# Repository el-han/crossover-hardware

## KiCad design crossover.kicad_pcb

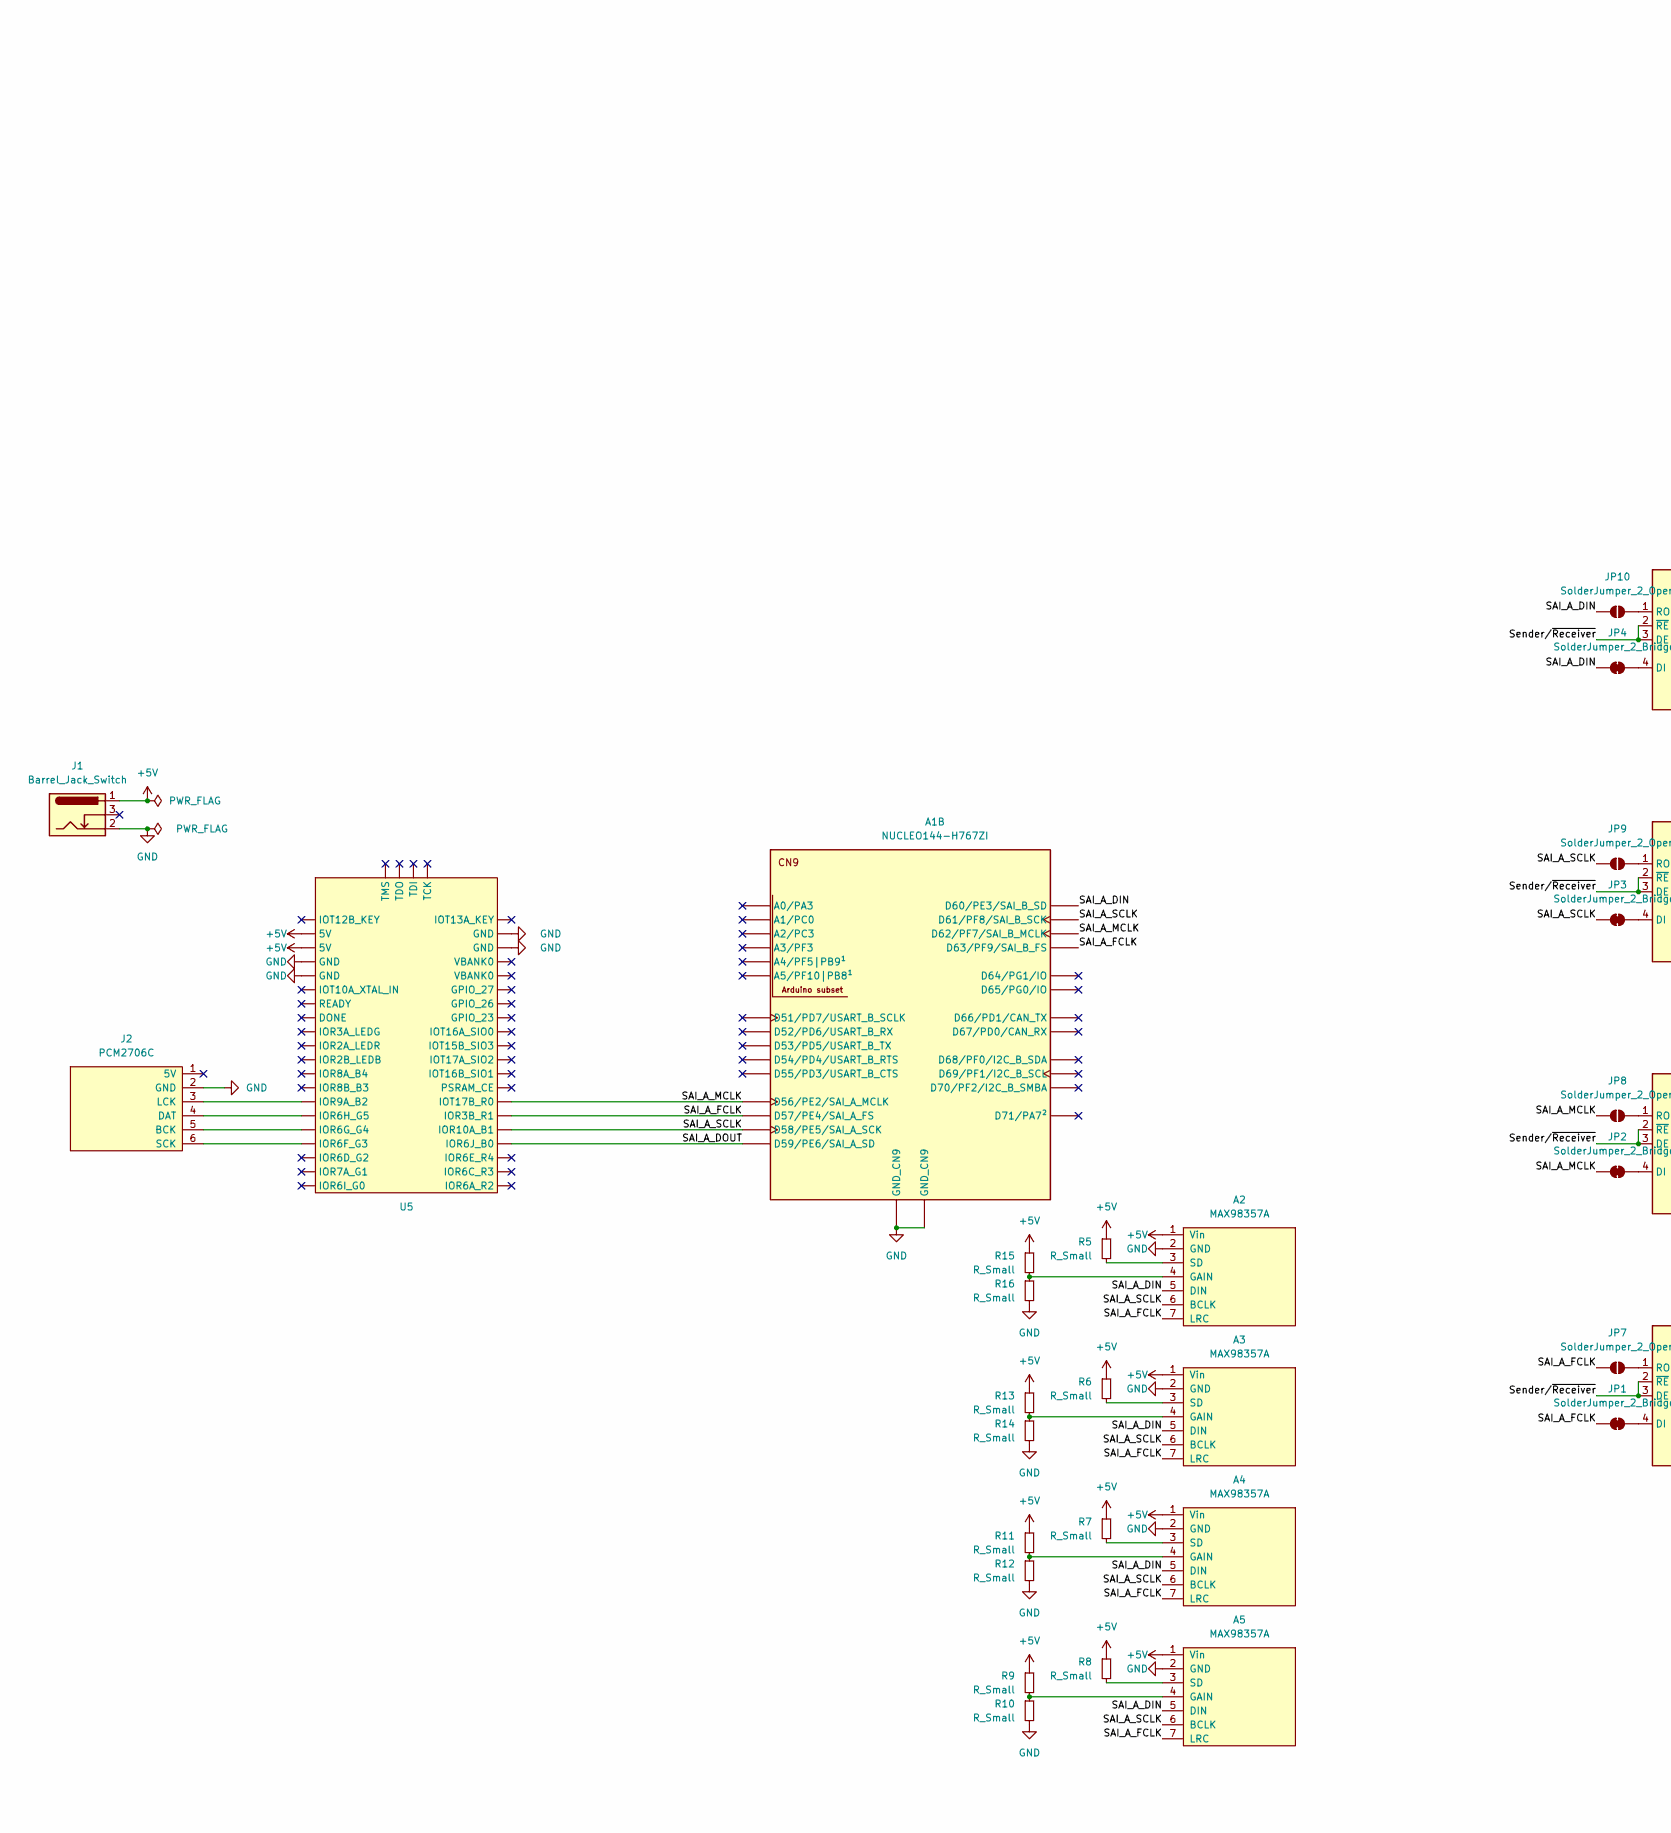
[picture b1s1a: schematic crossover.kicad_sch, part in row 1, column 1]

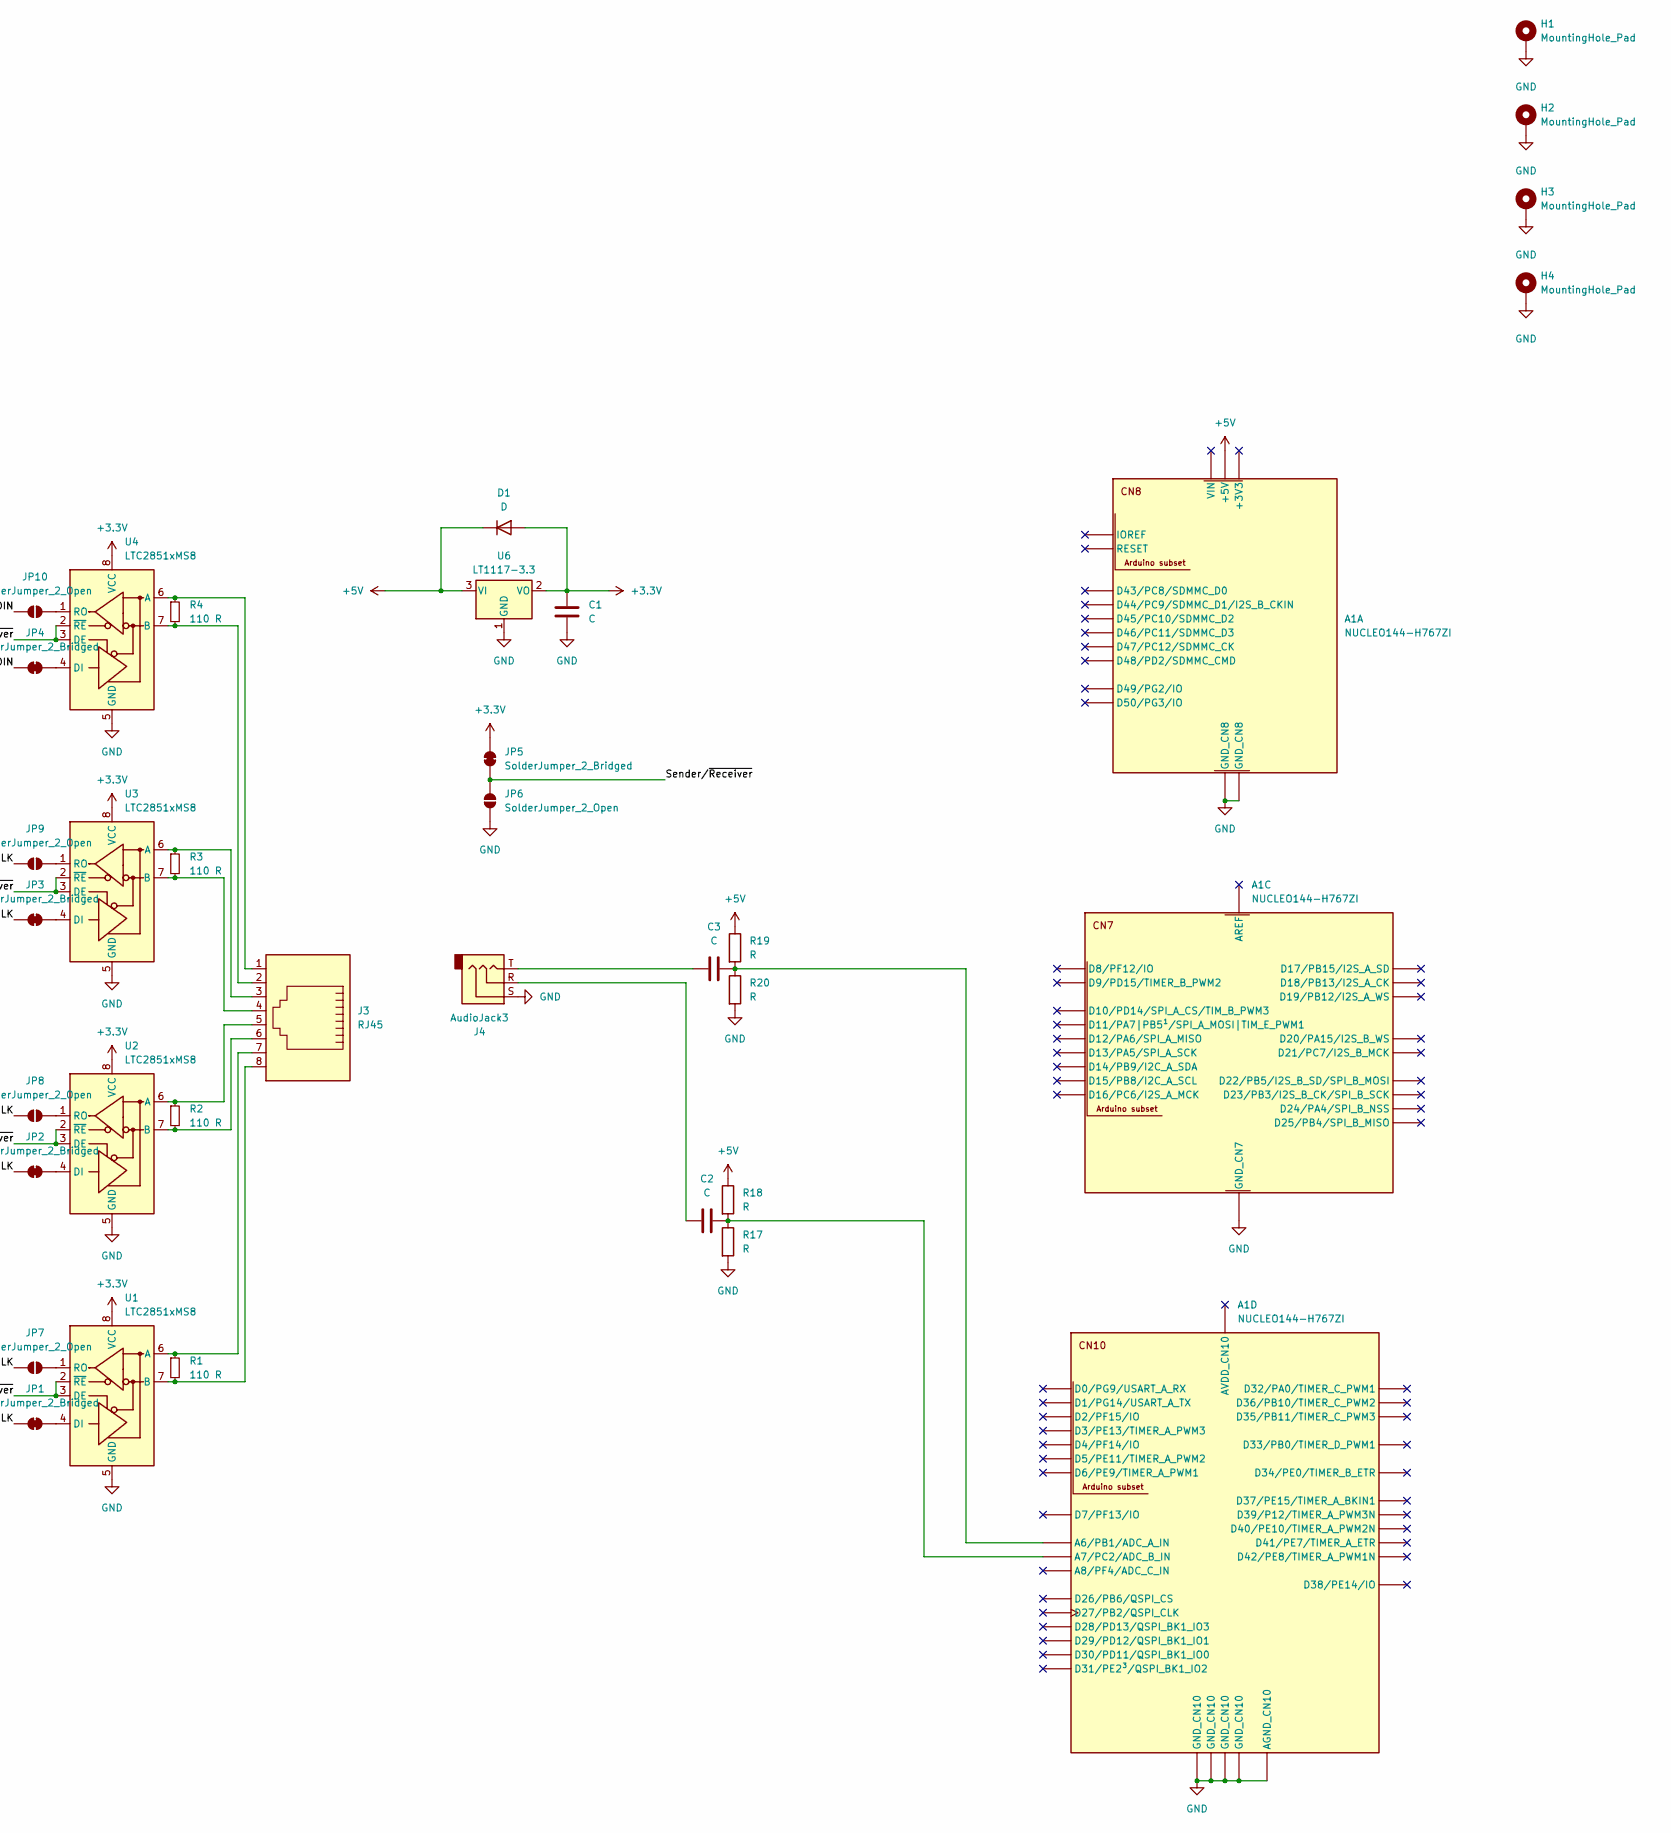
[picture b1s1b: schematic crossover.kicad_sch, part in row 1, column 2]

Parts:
A1: NUCLEO144-H767ZI; ST_Zio_Connectors_144_STLink
A2, A3, A4, A5: MAX98357A; Adafruit MAX98357 Breakout
C1: C; C_0805_2012Metric
C2, C3: C; C_0603_1608Metric
D1: D; D_0805_2012Metric
H1, H2, H3, H4: MountingHole_Pad; MountingHole_3.2mm_M3_Pad_Via
J1: Barrel_Jack_Switch; BarrelJack_Wuerth_6941xx301002
J2: PCM2706C; PCM2706C_Module
J3: RJ45; RJ45_Amphenol_54602-x08_Horizontal
J4: AudioJack3; Jack_3.5mm_CUI_SJ1-3533NG_Horizontal
JP1, JP2, JP3, JP4, JP5: SolderJumper_2_Bridged; SolderJumper-2_P1.3mm_Bridged_Pad1.0x1.5mm
JP6, JP7, JP8, JP9, JP10: SolderJumper_2_Open; SolderJumper-2_P1.3mm_Open_TrianglePad1.0x1.5mm
R1, R2, R3, R4: 110 R; R_0603_1608Metric
R5, R6, R7, R8, R9, R10, R11, R12, R13, R14, R15, R16: R_Small; R_0603_1608Metric
R17, R18, R19, R20: R; R_0603_1608Metric
U1, U2, U3, U4: LTC2851xMS8; MSOP-8_3x3mm_P0.65mm
U5: Tang_Nano_1K
U6: LT1117-3.3; SOT-223-3_TabPin2

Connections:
+3.3V: C1.1, D1.2 (A), JP5.2 (B), U1.8 (VCC), U2.8 (VCC), U3.8 (VCC), U4.8 (VCC), U6.2 (VO)
+5V: A1.CN8_9 (+5V), A2.1 (Vin), A3.1 (Vin), A4.1 (Vin), A5.1 (Vin), D1.1 (K), J1.1, R5.1, R6.1, R7.1, R8.1, R9.1, R11.1, R13.1, R15.1, R18.1, R19.1, U5.18 (5V), U5.19 (5V), U6.3 (VI)
/SAI_A_DIN: A1.CN9_22 (D60/PE3/SAI_B_SD), A2.5 (DIN), A3.5 (DIN), A4.5 (DIN), A5.5 (DIN), JP4.1 (A), JP10.1 (A)
/SAI_A_DOUT: A1.CN9_20 (D59/PE6/SAI_A_SD), U5.41 (IOR6J_B0)
/SAI_A_FCLK: A1.CN9_16 (D57/PE4/SAI_A_FS), A1.CN9_28 (D63/PF9/SAI_B_FS), A2.7 (LRC), A3.7 (LRC), A4.7 (LRC), A5.7 (LRC), JP1.1 (A), JP7.1 (A), U5.39 (IOR3B_R1)
/SAI_A_MCLK: A1.CN9_14 (D56/PE2/SAI_A_MCLK), A1.CN9_26 (D62/PF7/SAI_B_MCLK), JP2.1 (A), JP8.1 (A), U5.38 (IOT17B_R0)
/SAI_A_SCLK: A1.CN9_18 (D58/PE5/SAI_A_SCK), A1.CN9_24 (D61/PF8/SAI_B_SCK), A2.6 (BCLK), A3.6 (BCLK), A4.6 (BCLK), A5.6 (BCLK), JP3.1 (A), JP9.1 (A), U5.40 (IOR10A_B1)
/Sender/~Receiver: JP5.1 (A), JP6.2 (B), U1.2 (~RE), U1.3 (DE), U2.2 (~RE), U2.3 (DE), U3.2 (~RE), U3.3 (DE), U4.2 (~RE), U4.3 (DE)
GND: A1.CN7_8 (GND_CN7), A1.CN8_11 (GND_CN8), A1.CN8_13 (GND_CN8), A1.CN9_12 (GND_CN9), A1.CN9_23 (GND_CN9), A1.CN10_3 (AGND_CN10), A1.CN10_5 (GND_CN10), A1.CN10_17 (GND_CN10), A1.CN10_22 (GND_CN10), A1.CN10_27 (GND_CN10), A2.2 (GND), A3.2 (GND), A4.2 (GND), A5.2 (GND), C1.2, H1.1, H2.1, H3.1, H4.1, J1.2, J2.2 (GND), J4.S, JP6.1 (A), R10.2, R12.2, R14.2, R16.2, R17.2, R20.2, U1.5 (GND), U2.5 (GND), U3.5 (GND), U4.5 (GND), U5.16 (GND), U5.17 (GND), U5.26 (GND), U5.27 (GND), U6.1 (GND)
unnamed: A1.CN10_7 (A6/PB1/ADC_A_IN), C3.2, R19.2, R20.1
unnamed: A1.CN10_9 (A7/PC2/ADC_B_IN), C2.2, R17.1, R18.2
unnamed: A2.4 (GAIN), R15.2, R16.1
unnamed: A2.3 (SD), R5.2
unnamed: A3.4 (GAIN), R13.2, R14.1
unnamed: A3.3 (SD), R6.2
unnamed: A4.4 (GAIN), R11.2, R12.1
unnamed: A4.3 (SD), R7.2
unnamed: A5.4 (GAIN), R9.2, R10.1
unnamed: A5.3 (SD), R8.2
unnamed: C2.1, J4.R
unnamed: C3.1, J4.T
unnamed: J2.5 (BCK), U5.5 (IOR6G_G4)
unnamed: J2.4 (DAT), U5.6 (IOR6H_G5)
unnamed: J2.3 (LCK), U5.7 (IOR9A_B2)
unnamed: J2.6 (SCK), U5.4 (IOR6F_G3)
unnamed: JP1.2 (B), U1.4 (DI)
unnamed: JP2.2 (B), U2.4 (DI)
unnamed: JP3.2 (B), U3.4 (DI)
unnamed: JP4.2 (B), U4.4 (DI)
unnamed: JP7.2 (B), U1.1 (RO)
unnamed: JP8.2 (B), U2.1 (RO)
unnamed: JP9.2 (B), U3.1 (RO)
unnamed: JP10.2 (B), U4.1 (RO)
unnamed: J3.7, R1.1, U1.6 (A)
unnamed: J3.8, R1.2, U1.7 (B)
unnamed: J3.5, R2.1, U2.6 (A)
unnamed: J3.6, R2.2, U2.7 (B)
unnamed: J3.3, R3.1, U3.6 (A)
unnamed: J3.4, R3.2, U3.7 (B)
unnamed: J3.1, R4.1, U4.6 (A)
unnamed: J3.2, R4.2, U4.7 (B)

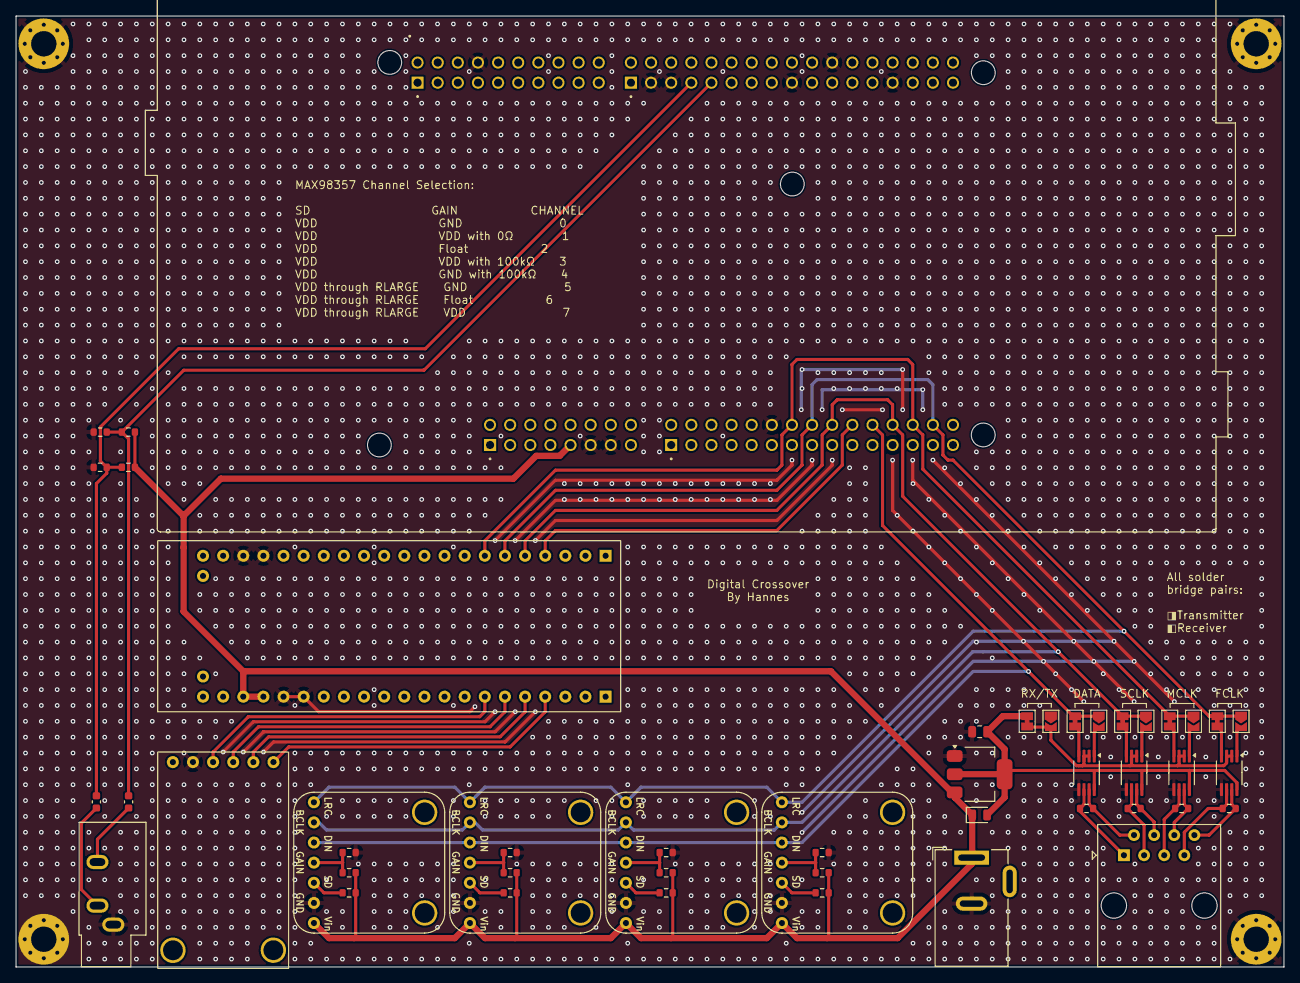
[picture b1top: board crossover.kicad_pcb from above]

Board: 2 copper layers, 160.0 x 120.0 mm, 53 parts (0 on the bottom side), 41 nets.

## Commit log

2024-10-14 add gerber zip to Makefile
